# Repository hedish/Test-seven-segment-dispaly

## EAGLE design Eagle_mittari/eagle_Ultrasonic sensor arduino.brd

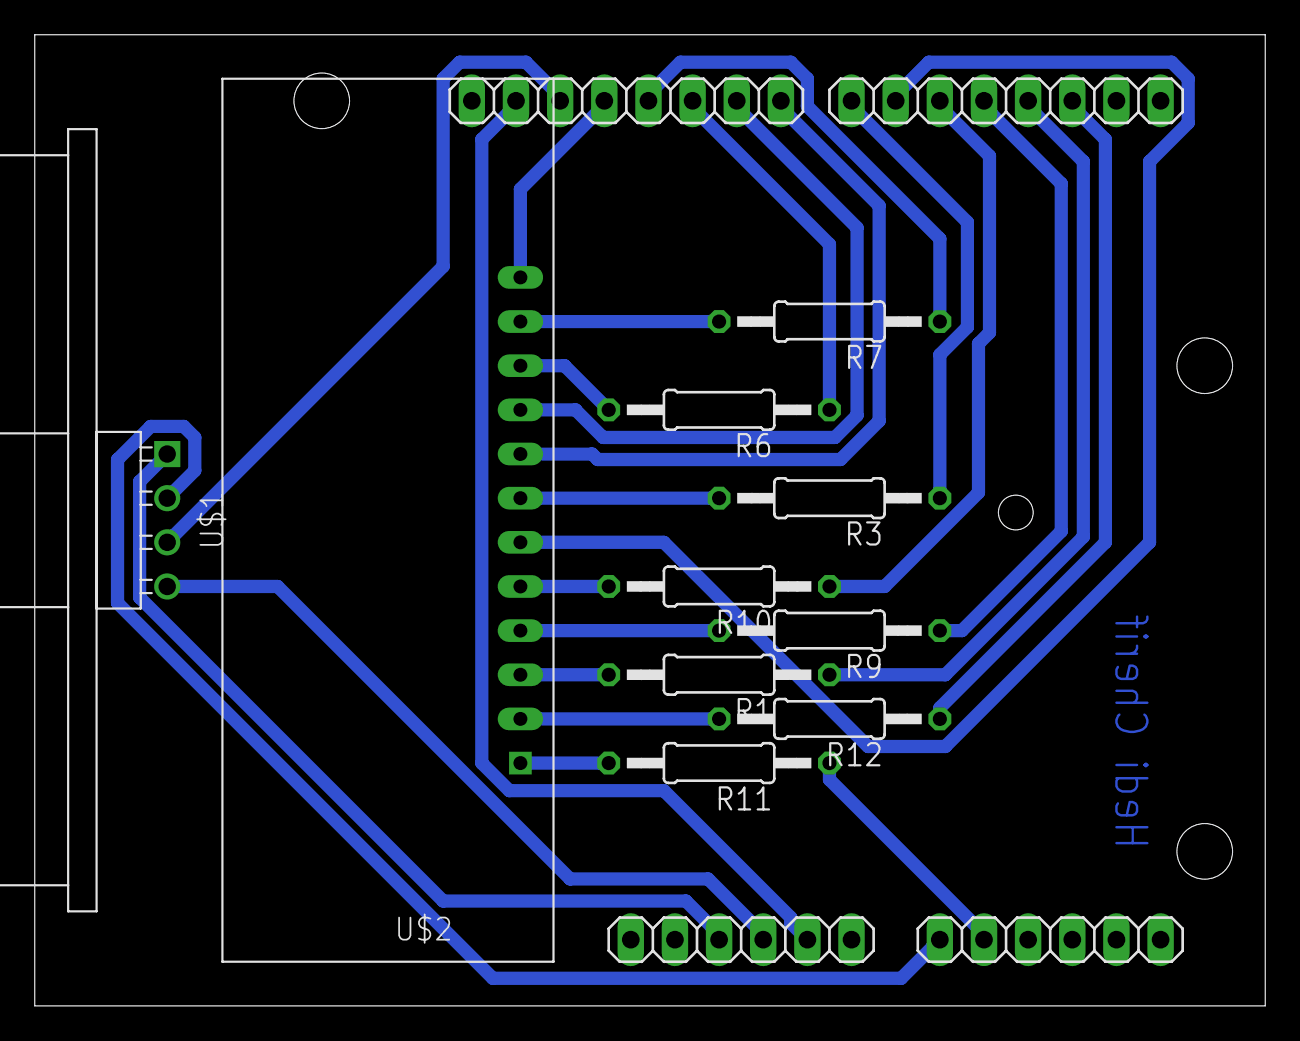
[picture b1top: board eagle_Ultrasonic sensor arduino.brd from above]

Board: 2 copper layers, 70.8 x 55.9 mm, 11 parts (0 on the bottom side), 25 nets.

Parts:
IC2: ARDUINO2009
R1, R9, R10, R11, R12: 150; 0207/12
R3, R6, R7: 0207/12
U$1: ULTRASONIC-HC-SR04#V
U$2: KW4-563ASA; NFD-5641

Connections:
GND: IC2.5, IC2.27
unnamed: R7.2, U$2.P$11
unnamed: R3.2, U$2.P$7
unnamed: R9.2, U$2.P$4
unnamed: R12.2, U$2.P$2
unnamed: IC2.7, U$1.2
unnamed: R6.2, U$2.P$10
unnamed: R10.2, U$2.P$5
unnamed: R1.2, U$2.P$3
unnamed: IC2.25, U$2.P$12
unnamed: IC2.22, U$2.P$9
unnamed: IC2.21, U$2.P$8
unnamed: IC2.19, U$2.P$6
unnamed: IC2.4, U$1.4
unnamed: IC2.3, U$1.1
unnamed: IC2.8, R11.1
unnamed: IC2.26, U$1.3
unnamed: IC2.24, R7.1
unnamed: IC2.23, R6.1
unnamed: IC2.20, R3.1
unnamed: IC2.15, R12.1
unnamed: IC2.16, R1.1
unnamed: IC2.17, R9.1
unnamed: IC2.18, R10.1
unnamed: R11.2, U$2.P$1

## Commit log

2020-01-08 Laitteisto todettu toimivaksi. Nelinumeroinen luku näytöllä
2020-01-08 Nelimerkkisen numeron syöttö valmiina
2020-01-14 show funktio rakenettu
2020-01-16 mittaus käynnistettu
2020-01-22 näytän kirjasto valmistus
2020-01-30 valmistus
2020-01-30 valmistus2

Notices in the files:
parts and their libraries:
diy-modules: Released under the Creative Commons Attribution 4.0 International License: http://creativecommons.org/licenses/by/4.0
